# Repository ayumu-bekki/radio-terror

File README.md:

RADIO TERROR

トランシーバー(特小無線)で生成AIナビゲーターと交信しながら、
風船入りの模擬爆弾(Core)を解体するハンズオン。

## ドキュメント

- [ゲームセッション設計 (Core)](docs/game_session_design.md)
- [radio-bridge 接続設計](docs/bridge_connection_design.md)
- [体験運用フロー](docs/operation_flow.md)
- [謎解きステージ集](docs/puzzle_stage_ideas.md)
- [ナビゲーター設計](docs/navigator_design.md)
- [シナリオテンプレート設計](docs/scenario_design.md)
- [紙資料(別紙)制作仕様](docs/printed_materials.md)
- **[マネージャー運用マニュアル](docs/manager_manual.md)** — 当日の運営手順(現場で見る)

設計は確定済み(2026-08-08)。実装は設計に沿って完了している(2026-08-09)。

## 構成

```
[core-system (複数台)] ──WebSocket /ws──▶ [game-server] ◀── gRPC ── [radio-bridge (複数)]
                                              │
                                          [Valkey]  ナビゲーター(生成AI)・混線演出
```

周辺機器(Core・radio-bridge)はいずれも **サーバーへダイヤルインする**。
サーバーは周辺機器のアドレスを一切管理しない。

| コンポーネント | 言語 | 役割 |
|---|---|---|
| `app/core-system` | C++ (ESP-IDF) | Core本体。セッションJSONを受け取り単体でゲームを完遂する |
| `app/game-server` | Go | セッション組み立て・ナビゲーター・混線・永続化・Management Console |

**編集して再起動すれば反映される設定**(再ビルド不要):

| 場所 | 内容 |
|---|---|
| `app/game-server/scenarios/` | ステージ定義・難易度テンプレート |
| `app/game-server/navigator/` | ナビゲーターのキャラクター・プロンプト |
| `app/game-server/config.toml` | モデル・接続先・紙資料の物理定数など |
| `app/radio-bridge` | Rust | 特小無線とのPTT制御・音声入出力(Raspberry Pi) |
| `app/radio-bridge-emulator` | Go | radio-bridge の代替(PCのマイク・スピーカーを使う) |
| `app/radio-bridge-test-client` | Go | 動作確認用CLI(1つのbridgeとして振る舞う) |

## 動かす

```bash
cd app
cp game-server/config.sample.toml game-server/config.toml  # project/location を設定する
docker compose up
```

- マネージャー向け画面: <http://localhost:8080/manager>
- Core (core-system) の接続先とCoreIDは `idf.py menuconfig` の
  "Core System Configuration" で設定する(CoreIDは数字4桁)。

radio-bridge はチーム(周波数)ごとに1プロセス動かす。プロセスごとに変わる設定は
環境変数で指定し、`config.toml` は共有する:

| 環境変数 | 内容 |
|---|---|
| `RADIO_BRIDGE_ID` | この bridge の ID |
| `RADIO_BRIDGE_INPUT_DEVICE` | マイク側のオーディオIF (例 `hw:2,0`) |
| `RADIO_BRIDGE_OUTPUT_DEVICE` | スピーカー側のオーディオIF (例 `plughw:2,0`) |

デバイス名は実機で `aplay -l` / `arecord -l` で確認する。
チームを増やす場合は `compose.yaml` の `environment` だけ変えた
サービスを追加する。

## 制作物(コンテンツ)

コードとは別に、以下の制作が必要:

- 紙資料: モールス対照表・記号/数字シート・回路図シート・CoreID銘板。
  **印刷する表の中身と制作要件は [`docs/printed_materials.md`](docs/printed_materials.md)**
- 混線音声・効果音アセット(`app/game-server/assets/README.md` に
  ファイル名規約とセリフ一覧)

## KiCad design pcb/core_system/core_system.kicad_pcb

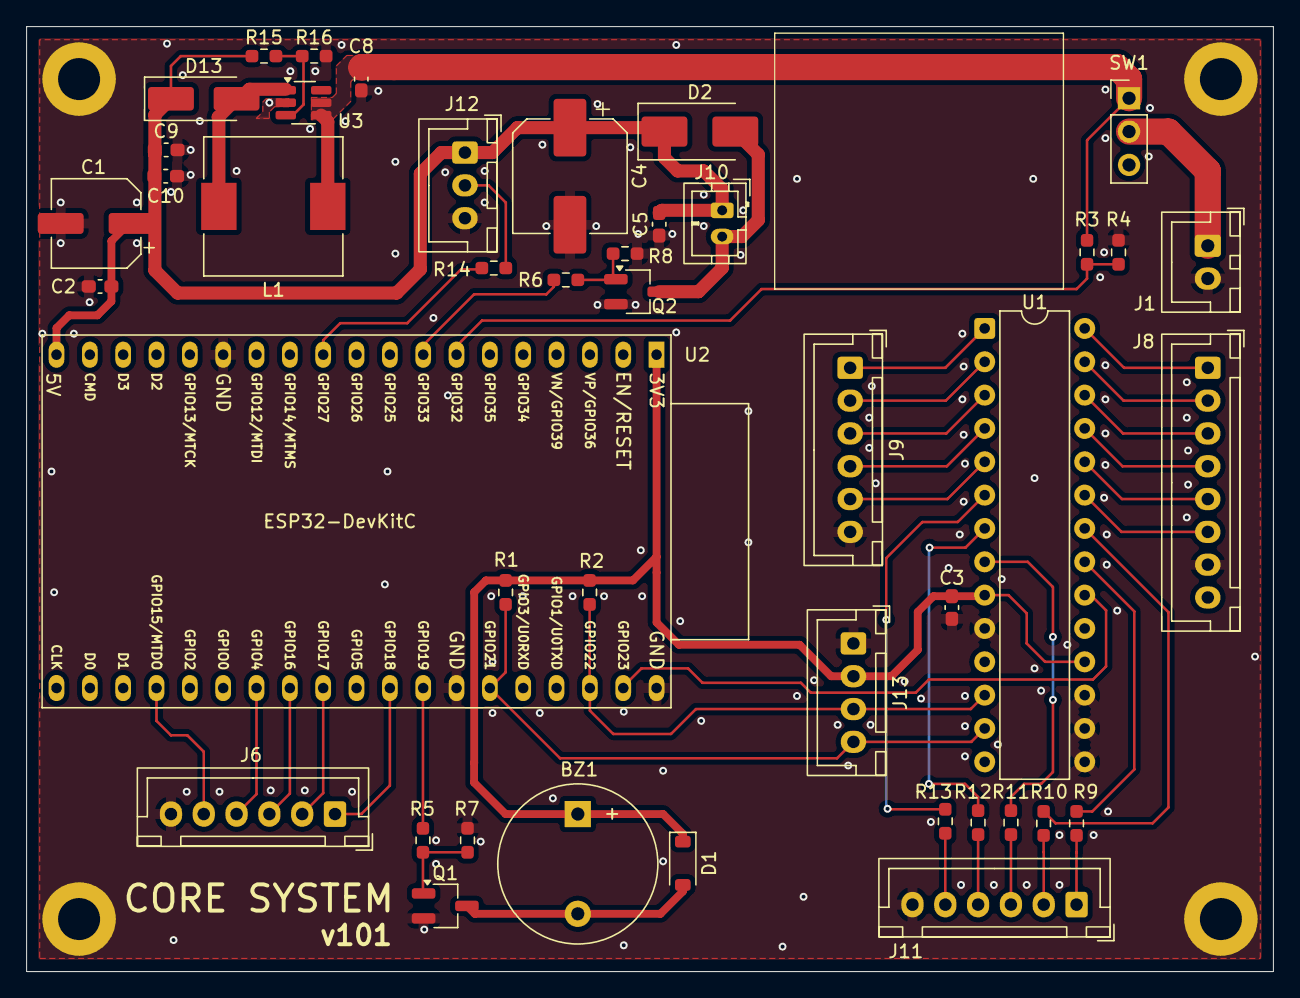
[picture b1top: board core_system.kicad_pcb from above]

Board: 2 copper layers, 95.0 x 72.0 mm, 47 parts (0 on the bottom side), 45 nets.

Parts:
BZ1: Buzzer; Buzzer_12x9.5RM7.6
C1: 100μ; CP_Elec_6.3x5.8
C2, C3, C5: 0.1μ; C_0603_1608Metric_Pad1.08x0.95mm_HandSolder
C4: 470μ; CP_Elec_8x10.5
C8: 10μ; C_0603_1608Metric_Pad1.08x0.95mm_HandSolder
C9, C10: 22μ; C_0603_1608Metric_Pad1.08x0.95mm_HandSolder
D1: 1N5819; D_SOD-123
D2: SS34; D_SMB_Handsoldering
D13: SS34; D_SMA_Handsoldering
H1, H2, H3, H4: MountingHole_Pad; MountingHole_3.2mm_M3_DIN965_Pad
J1: Battery; JST_XH_B2B-XH-A_1x02_P2.50mm_Vertical
J6, J9, J11: Conn_01x06_Pin; JST_XH_B6B-XH-A_1x06_P2.50mm_Vertical
J8: Conn_01x08_Pin; JST_XH_B8B-XH-A_1x08_P2.50mm_Vertical
J10: Conn_01x02_Pin; JST_PH_B2B-PH-K_1x02_P2.00mm_Vertical
J12: Conn_01x03_Pin; JST_XH_B3B-XH-A_1x03_P2.50mm_Vertical
J13: LED Segment; JST_XH_B4B-XH-A_1x04_P2.50mm_Vertical
L1: 22μ; L_10.4x10.4_H4.8
Q1: 2SC2712-Y; SC-59_Handsoldering
Q2: IRLML6344TRPBF; SC-59_Handsoldering
R1, R2, R7, R8, R12: 10k; R_0603_1608Metric_Pad0.98x0.95mm_HandSolder
R3, R4, R15: 220k; R_0603_1608Metric_Pad0.98x0.95mm_HandSolder
R5, R9, R10, R11, R13: 1k; R_0603_1608Metric_Pad0.98x0.95mm_HandSolder
R6: 100; R_0603_1608Metric_Pad0.98x0.95mm_HandSolder
R14: 330; R_0603_1608Metric_Pad0.98x0.95mm_HandSolder
R16: 30k; R_0603_1608Metric_Pad0.98x0.95mm_HandSolder
SW1: SW_SPDT; PinHeader_1x03_P2.54mm_Vertical
U1: MCP23017x-x-SP; DIP-28_W7.62mm
U2: ESP32-DevKitC
U3: MT3608; SOT-23-6_Handsoldering

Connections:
+3.3V: BZ1.1 (+), C3.1, D1.1 (K), J13.2, R1.1, R2.1, U1.9 (V_{DD}), U1.18 (~RESET), U2.1 (3V3)
+5V: C1.1, C2.2, C4.1, C5.2, C9.1, C10.1, D2.1 (K), D13.1 (K), J10.1, J12.1, R15.1, U2.19 (5V)
+BATT: J1.1, SW1.2 (B)
Battery ADC: R3.1, R4.2, U2.7 (32K_XP/GPIO32/ADC1_CH4)
Buzzer Out: R5.1, U2.31 (GPIO19)
ExIO Interrupt: U1.20 (INTA), U2.37 (GPIO23)
FullColorLED: R14.1, U2.11 (ADC2_CH7/GPIO27)
GND: C1.2, C2.1, C3.2, C4.2, C5.1, C8.2, C9.2, C10.2, H1.1 (1_1), H2.1 (1_1), H3.1 (1_1), H4.1 (1_1), J1.2, J6.6, J8.7, J9.6, J11.6, J12.3, J13.1, Q1.2 (E), Q2.2 (S), R4.1, R7.2, R8.2, R16.2, U1.10 (V_{SS}), U1.15 (A0), U1.16 (A1), U1.17 (A2), U2.14 (GND), U2.32 (GND), U2.38 (GND), U3.2 (GND)
I2C SCL: J13.3, R2.2, U1.12 (SCK), U2.36 (GPIO22)
I2C SDA: J13.4, R1.2, U1.13 (SDA), U2.33 (GPIO21)
LED A: R9.1, U1.21 (GPA0)
LED B: R10.1, U1.22 (GPA1)
LED C: R11.1, U1.8 (GPB7)
LED D: R12.1, U1.7 (GPB6)
LED E: R13.1, U1.6 (GPB5)
Line A: J6.1, U2.30 (GPIO18)
Line B: J6.2, U2.28 (GPIO17)
Line C: J6.3, U2.27 (GPIO16)
Line D: J6.4, U2.26 (ADC2_CH0/GPIO4)
Line E: J6.5, U2.23 (MTDO/GPIO15/ADC2_CH3)
unnamed: BZ1.2 (-), D1.2 (A), Q1.3 (C)
unnamed: D2.2 (A), J10.2, Q2.3 (D)
unnamed: D13.2 (A), L1.2, U3.1 (SW)
unnamed: J11.1, R9.2
unnamed: J11.2, R10.2
unnamed: J11.3, R11.2
unnamed: J11.4, R12.2
unnamed: J11.5, R13.2
unnamed: J12.2, R14.2
unnamed: Q1.1 (B), R5.2, R7.1
unnamed: Q2.1 (G), R6.2, R8.1
unnamed: C8.1, L1.1, R3.2, SW1.1 (A), U3.4 (EN), U3.5 (IN)
unnamed: R15.2, R16.1, U3.3 (FB)
Push A: J9.1, U1.1 (GPB0)
Push B: J9.2, U1.2 (GPB1)
Push C: J9.3, U1.3 (GPB2)
Push D: J9.4, U1.4 (GPB3)
Push E: J9.5, U1.5 (GPB4)
Rotary1: J8.1, U1.28 (GPA7)
Rotary2: J8.2, U1.27 (GPA6)
Rotary3: J8.3, U1.26 (GPA5)
Rotary4: J8.4, U1.25 (GPA4)
Rotary5: J8.5, U1.24 (GPA3)
Rotary6: J8.6, U1.23 (GPA2)
Solenoid Out: R6.1, U2.8 (32K_XN/GPIO33/ADC1_CH5)

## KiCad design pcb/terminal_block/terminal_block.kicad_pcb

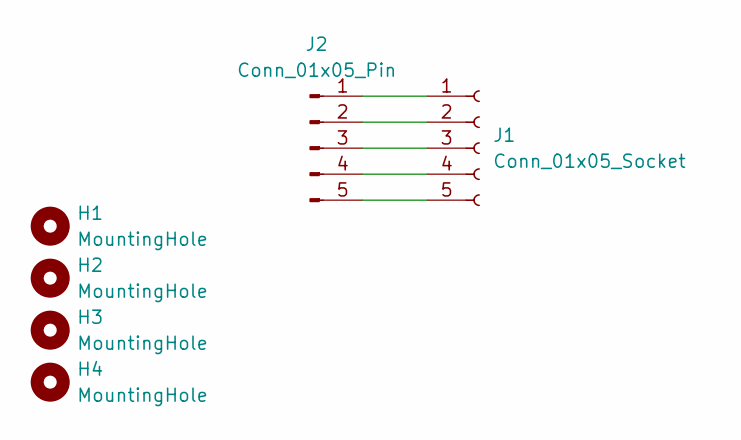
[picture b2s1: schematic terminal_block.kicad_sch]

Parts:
H1, H2, H3, H4: MountingHole; MountingHole_3.2mm_M3_ISO14580
J1: Conn_01x05_Socket; TB401-1-5-E
J2: Conn_01x05_Pin; PinHeader_1x05_P2.54mm_Vertical

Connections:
unnamed: J1.1, J2.1
unnamed: J1.2, J2.2
unnamed: J1.3, J2.3
unnamed: J1.4, J2.4
unnamed: J1.5, J2.5

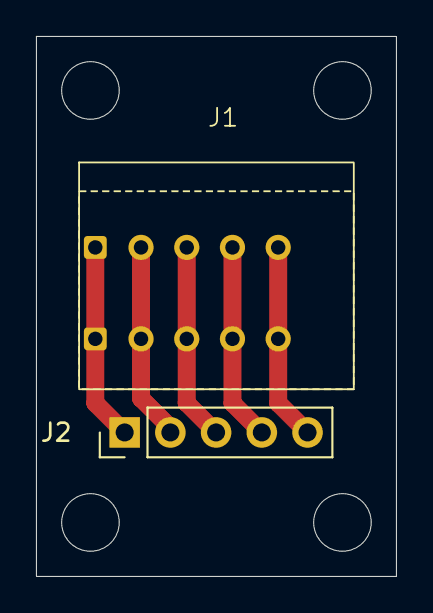
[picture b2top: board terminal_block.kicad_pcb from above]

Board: 2 copper layers, 20.0 x 30.0 mm, 6 parts (0 on the bottom side), 5 nets.

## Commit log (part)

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2026-06-23 fixname
2026-06-23 update curcuit
2026-06-23 fix adc pin
2026-06-23 danget_gadget_systemを追加しWS周りを整理
2026-06-24 fix Danger Gadget Curcuit. add tranceiver_connector kicad file
